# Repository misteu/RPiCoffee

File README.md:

# RPiCoffee aka Coffee as a Service 4 real
Modding / hacking of a coffee machine (DeLonghi ECAM 22.110.B Magnifica S) for IoT capabilities 

See github-Page or docs/README.md for working progress: https://misteu.github.io/RPiCoffee/

Here is everything a little bit more detailed: https://github.com/misteu/RPiCoffee/wiki (<-- still a lot of stuff missing, coming soon!)

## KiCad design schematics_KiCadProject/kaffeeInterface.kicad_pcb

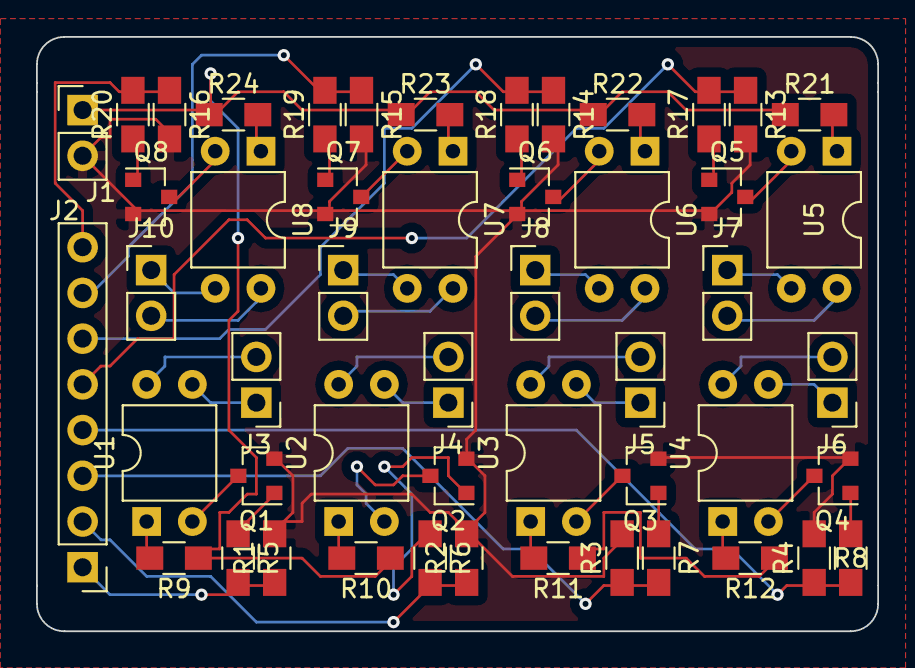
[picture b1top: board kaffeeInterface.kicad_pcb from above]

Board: 2 copper layers, 46.7 x 33.0 mm, 50 parts (0 on the bottom side), 50 nets.

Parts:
J1, J3, J4, J5, J6, J7, J8, J9, J10: Conn_01x02_Male; Pin_Header_Straight_1x02_Pitch2.54mm
J2: Conn_01x08_Male; Pin_Header_Straight_1x08_Pitch2.54mm
Q1, Q2, Q3, Q4, Q5, Q6, Q7, Q8: BC847; SOT-23
R1, R2, R3, R4, R13, R14, R15, R16: 10k; R_0805_HandSoldering
R5, R6, R7, R8, R17, R18, R19, R20: 5,6k; R_0805_HandSoldering
R9, R10, R11, R12, R21, R22, R23, R24: 200; R_0805_HandSoldering
U1, U2, U3, U4, U5, U6, U7, U8: LTV-817; DIP-4_W7.62mm

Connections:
+5V: J1.1, R9.1, R10.1, R11.1, R12.1, R21.1, R22.1, R23.1, R24.1
GND: J1.2, Q1.2, Q2.2, Q3.2, Q4.2, Q5.2, Q6.2, Q7.2, Q8.2, R1.2, R2.2, R3.2, R4.2, R13.2, R14.2, R15.2, R16.2
unnamed: J2.1, R1.1, R5.2
unnamed: J2.2, R2.1, R6.2
unnamed: J2.3, R3.1, R7.2
unnamed: J2.4, R4.1, R8.2
unnamed: J2.5, R13.1, R17.2
unnamed: J2.6, R14.1, R18.2
unnamed: J2.7, R15.1, R19.2
unnamed: J2.8, R16.1, R20.2
unnamed: J3.1, U1.3
unnamed: J3.2, U1.4
unnamed: J4.1, U2.3
unnamed: J4.2, U2.4
unnamed: J5.1, U3.3
unnamed: J5.2, U3.4
unnamed: J6.1, U4.3
unnamed: J6.2, U4.4
unnamed: J7.1, U5.3
unnamed: J7.2, U5.4
unnamed: J8.1, U6.3
unnamed: J8.2, U6.4
unnamed: J9.1, U7.3
unnamed: J9.2, U7.4
unnamed: J10.1, U8.3
unnamed: J10.2, U8.4
unnamed: Q1.1, R5.1
unnamed: Q1.3, U1.2
unnamed: Q2.1, R6.1
unnamed: Q2.3, U2.2
unnamed: Q3.1, R7.1
unnamed: Q3.3, U3.2
unnamed: Q4.1, R8.1
unnamed: Q4.3, U4.2
unnamed: Q5.1, R17.1
unnamed: Q5.3, U5.2
unnamed: Q6.1, R18.1
unnamed: Q6.3, U6.2
unnamed: Q7.1, R19.1
unnamed: Q7.3, U7.2
unnamed: Q8.1, R20.1
unnamed: Q8.3, U8.2
unnamed: R9.2, U1.1
unnamed: R10.2, U2.1
unnamed: R11.2, U3.1
unnamed: R12.2, U4.1
unnamed: R21.2, U5.1
unnamed: R22.2, U6.1
unnamed: R23.2, U7.1
unnamed: R24.2, U8.1

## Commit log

2018-02-03 Update and rename LICENSE to LICENSE_BSD3Clause
2018-02-03 Create LICENSE_Python_PSF
2018-02-03 Update and rename LICENSE_BSD3Clause to LICENSE_Flask_BSD3
2018-02-03 images uploaded
2018-02-03 name changes
2018-02-03 deleted image
2018-02-03 Set theme jekyll-theme-merlot
2018-02-03 Set theme jekyll-theme-tactile
2018-02-03 Set theme jekyll-theme-cayman
2018-02-03 Rename README.md to README.html
2018-02-03 Rename README.html to README.md
2018-02-03 Rename page1.md to README.md
2018-02-03 changed directory
2018-02-03 changed path
2018-02-03 added image
2018-02-03 updated image
2018-02-03 moved shoppinglist
2018-02-03 Rename shoppingList.txt to shoppingList.md
2018-02-03 gifs added
2018-02-03 Update LICENSE_Flask_BSD3
2018-02-03 Create LICENSE
2018-02-07 added UI-Prototype images
2018-02-07 renamed UI-Prototype images
2018-02-08 added images
2018-02-08 updated images
2018-02-21 update enamelled copper wires
2018-02-22 skeleton powered UI finished
2018-02-22 updated UI
2018-02-22 UI Gif
2018-02-22 added UI img
2018-02-23 UI update
2018-02-23 update UI
2018-02-23 update UI responsiveness
2018-02-23 UI BG fix
2018-02-23 merge
2018-02-23 buttons svgtext --> html
2018-03-11 Flask UI added
2018-03-14 added XMG Miner
2018-03-15 img resize
2018-03-15 updated minig info
2018-03-15 updated mining info
2018-03-15 resized images
2018-03-15 UI img added
2018-03-15 updated UI img extension
2018-03-15 new images
2018-03-15 added mining img
2018-03-18 added Metro-API+Weather-API
2018-03-18 added UI screenshots
2018-03-20 added mongoDB Access: write every user action to RPi's mongoDB, read in UI
2018-10-27 added schematics
2018-10-27 added image of missed routing
2018-10-27 added PDF of schematic
2018-10-27 added gerber plots
2018-10-27 added bom
2018-10-27 added image of shopping list
2018-10-27 added Torx images
2018-10-27 pics resized
2018-11-12 Screenshot 3D PCB
2019-09-26 added annotated pcb
2025-08-16 updated URL for rasp minimal setup (previous link dead or not available everywhere)

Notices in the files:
schematics_KiCadProject/kaffeeInterface.kicad_pcb:
:  .____,  : (c) 2018 c.mic.st
